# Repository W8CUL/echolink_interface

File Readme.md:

# Echolink installation 

By KE8TJE

- Documenting basic steps starting from the installation of svxlink

## Installation steps

1. Install svxlink `sudo apt install svxlink`
2. Disable the internal audio drivers `<cmd needed>`
## Debug steps and details

## Todo list

- [ ] Echolink login
- [x] DRA818V testing interface - June 2025
- [ ] Mqtt kill switch implimentation (svxlink stop)
- [ ] DTMF kill switch installation
- [x] DRA 818V PCB - Completed June 2025

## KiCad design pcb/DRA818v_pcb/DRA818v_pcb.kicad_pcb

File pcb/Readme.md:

## V1.0 Schematic

- Using DRA818V as the radio module
- An External USB sound card as the audio interface
- An external FTDI USB cable as the radio interface

## PCB layout 

### Component list 

## TODO

- [ ] External fan control via GPIO pins
- [ ] External kill switch via GPIO pins
- [ ] Temp monitor using a DS18B20

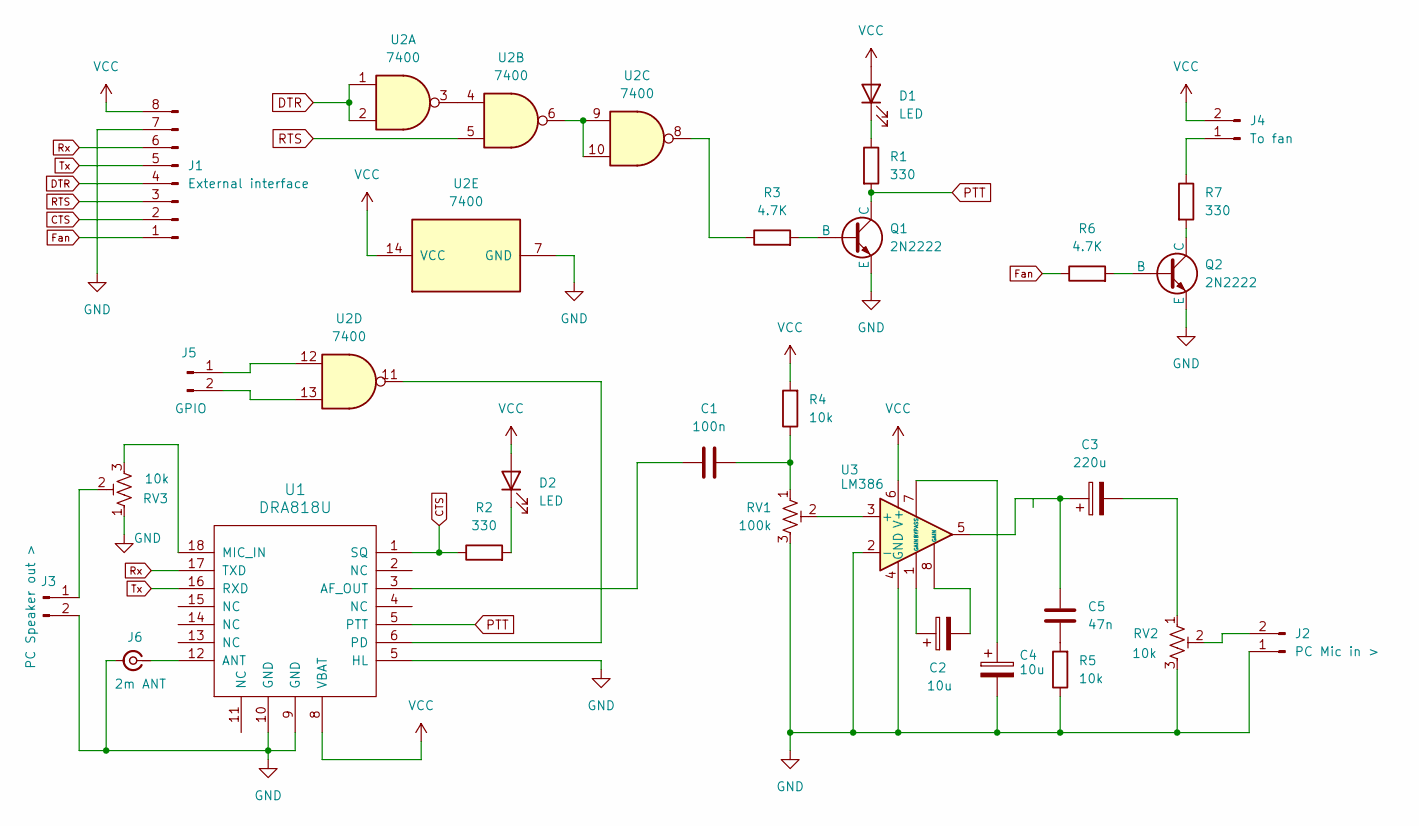
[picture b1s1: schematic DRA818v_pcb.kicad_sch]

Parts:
C1: 100n; C_Disc_D4.7mm_W2.5mm_P5.00mm
C2, C4: 10u; CP_Radial_D4.0mm_P2.00mm
C3: 220u; CP_Radial_D8.0mm_P5.00mm
C5: 47n; C_Disc_D4.7mm_W2.5mm_P5.00mm
D1, D2: LED; LED_D5.0mm
J1: External interface; PinHeader_1x08_P2.54mm_Vertical
J2: PC Mic in >; PinHeader_1x02_P2.54mm_Vertical
J3: PC Speaker out >; PinHeader_1x02_P2.54mm_Vertical
J4: To fan; PinHeader_1x02_P2.54mm_Vertical
J5: GPIO; PinHeader_1x02_P2.54mm_Vertical
J6: 2m ANT; SMA_Amphenol_901-144_Vertical
Q1, Q2: 2N2222; TO-92L_Inline_Wide
R1: 330; R_Axial_DIN0204_L3.6mm_D1.6mm_P7.62mm_Horizontal
R2, R7: 330; R_Axial_DIN0207_L6.3mm_D2.5mm_P7.62mm_Horizontal
R3, R6: 4.7K; R_Axial_DIN0207_L6.3mm_D2.5mm_P7.62mm_Horizontal
R4, R5: 10k; R_Axial_DIN0207_L6.3mm_D2.5mm_P7.62mm_Horizontal
RV1: 100k; Potentiometer_Runtron_RM-065_Vertical
RV2, RV3: 10k; Potentiometer_Runtron_RM-065_Vertical
U1: DRA818U; DRA818
U2: 7400; DIP-14_W7.62mm
U3: LM386; DIP-8_W7.62mm

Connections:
CTS: J1.2, R2.1, U1.1 (SQ)
DTR: J1.4, U2.1, U2.2
Fan: J1.1, R6.1
unnamed: C1.2, R4.1, RV1.1
unnamed: C2.1, U3.1 (GAIN)
unnamed: C2.2, U3.8 (GAIN)
unnamed: C3.1, C5.2, U3.5
unnamed: C3.2, RV2.1
unnamed: C5.1, R5.2
unnamed: D1.1 (K), R1.1
unnamed: D2.1 (K), R2.2
unnamed: J2.2, RV2.2
unnamed: J3.1, RV3.2
unnamed: J4.1, R7.1
unnamed: J5.1, U2.12
unnamed: J5.2, U2.13
unnamed: J6.1 (In), U1.12 (ANT)
unnamed: Q1.2 (B), R3.2
unnamed: Q2.2 (B), R6.2
unnamed: Q2.1 (C), R7.2
unnamed: R3.1, U2.8
unnamed: C1.1, U1.3 (AF_OUT)
unnamed: RV3.3, U1.18 (MIC_IN)
unnamed: U1.6 (PD), U2.11
unnamed: U2.3, U2.4
unnamed: U2.6, U2.9, U2.10
unnamed: RV1.2, U3.3 (+)
unnamed: C4.1, U3.7 (BYPASS)
RTS: J1.3, U2.5
Rx: J1.6, U1.17 (TXD)
Tx: J1.5, U1.16 (RXD)
VCC: D1.2 (A), D2.2 (A), J1.8, J4.2, R4.2, U1.8 (VBAT), U2.14 (VCC), U3.6 (V+)

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
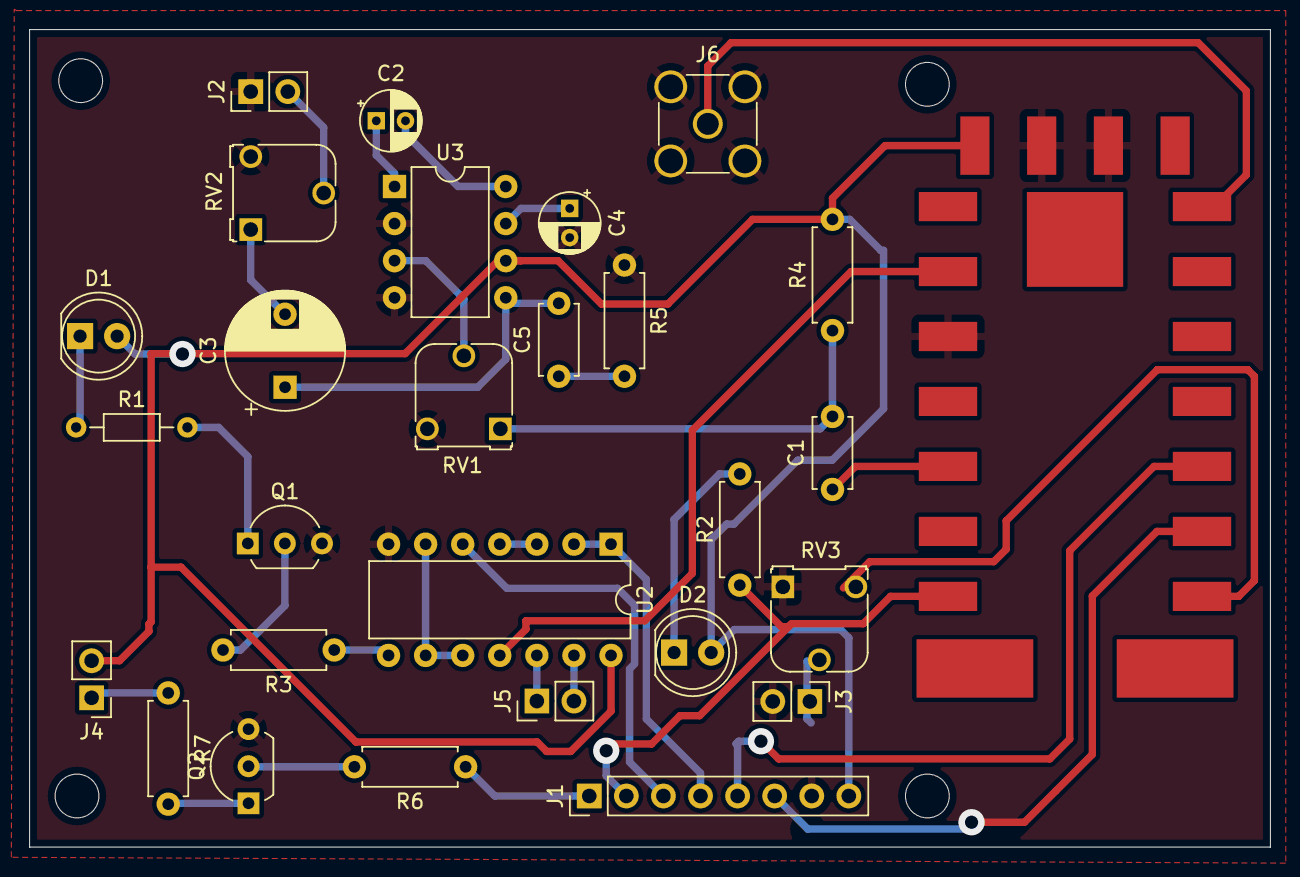
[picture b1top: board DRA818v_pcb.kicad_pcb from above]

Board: 2 copper layers, 85.0 x 56.0 mm, 28 parts (0 on the bottom side), 34 nets.

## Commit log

2025-06-15 added basic config files that are linked to the svxconfig untested
2025-06-15 vault backup: 2025-06-15 16:18:13
2025-06-15 vault backup: 2025-06-15 18:54:22
2025-06-15 vault backup: 2025-06-15 18:55:33
